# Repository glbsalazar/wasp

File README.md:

# WASP 
## Wireless Assisted Serial Port

---
***This is a Work in Progress***

---
### Motivation
The goal of this project is to have a serial to wireless converter that allows the read and write to a serial port over wifi.

This would allow access to remote devices that do not have a wifi connection or to debug devices that have a permanent serial port and can sometimes crash and lose wifi connectivity (ie: embedded linux systems).

As an end goal this should work in a "ssh" kind of way.

---
### Requirements

* Receive serial data over wifi
* Send serial data over wifi
* Possibiliy to configure the WiFi connection
* Powered over USB or 5V header
* Serial data interface directly on the device

---
### Current implementation
Currently it is based on a STM32 and a ESP-01 for wifi.

The current example works over a tcp connection with the WASP operating as a client.

The current example is based on a fork of the drogue-esp8266 crate with modifications to support version 2.1.0.0 of the ESP-AT firmware

---
## License

### Firmware:

Licensed under either of

- Apache License, Version 2.0 ([LICENSE-APACHE](LICENSE-APACHE) or
  http://www.apache.org/licenses/LICENSE-2.0)

- MIT license ([LICENSE-MIT](LICENSE-MIT) or http://opensource.org/licenses/MIT)

at your option.

### Hardware:

Licensed under CERN Open Hardware License Permissive, Version 2.0 ([LICENSE-CERN-OHL-P](LICENSE-CERN-OHL-P) or
https://ohwr.org/cern_ohl_p_v2.txt)

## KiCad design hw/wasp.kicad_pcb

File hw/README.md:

# WASP 
## Wireless Assisted Serial Port Hardware

---
***This is a Work in Progress***

---

The current design is based around a STM32F103 and has an ESP-01 as a wifi coprocessor

---
## License

Licensed under CERN Open Hardware License Permissive, Version 2.0 ([LICENSE-CERN-OHL-P](LICENSE-CERN-OHL-P) or https://ohwr.org/cern_ohl_p_v2.txt)

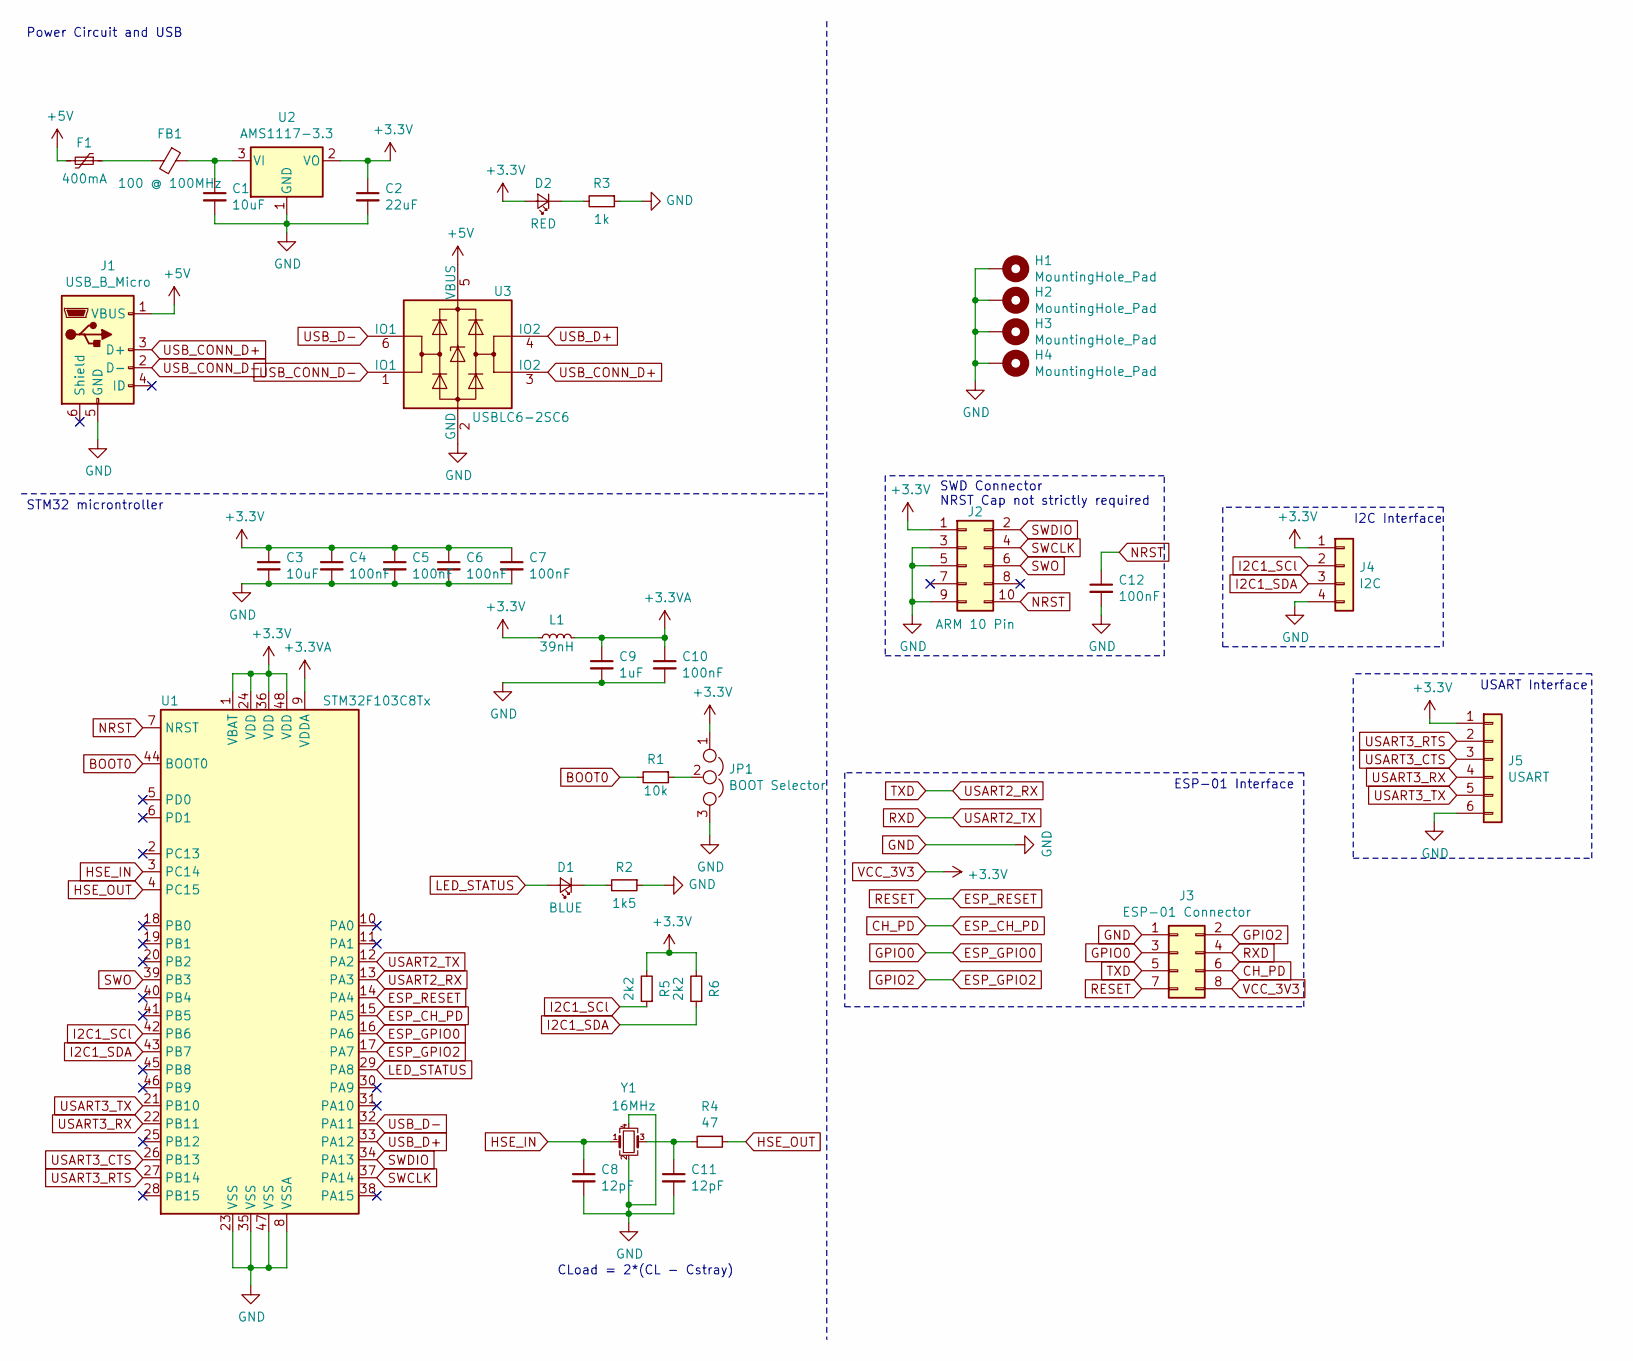
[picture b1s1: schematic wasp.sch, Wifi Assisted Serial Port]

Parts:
C1, C3: 10uF; C_0603_1608Metric; LCSC Part # C19702
C2: 22uF; C_0603_1608Metric; LCSC Part # C59461
C4, C5, C6, C7, C10, C12: 100nF; C_0402_1005Metric; LCSC Part # C1525
C8, C11: 12pF; C_0402_1005Metric; LCSC Part # C1547
C9: 1uF; C_0402_1005Metric; LCSC Part # C52923
D1: BLUE; LED_0603_1608Metric; LCSC Part # C72041
D2: RED; LED_0603_1608Metric; LCSC Part # C2286
F1: 400mA; Fuse_0603_1608Metric
FB1: 100 @ 100MHz; L_0805_2012Metric
H1, H2, H3, H4: MountingHole_Pad; MountingHole_2.2mm_M2_Pad_Via
J1: USB_B_Micro
J2: ARM 10 Pin; PinHeader_2x05_P1.27mm_Vertical_SMD
J3: ESP-01 Connector; PinHeader_2x04_P2.54mm_Vertical
J4: I2C; PinHeader_1x04_P2.54mm_Vertical
J5: USART; PinHeader_1x06_P2.54mm_Horizontal
JP1: BOOT Selector; PinHeader_1x03_P2.54mm_Vertical
L1: 39nH; L_0402_1005Metric
R1: 10k; R_0402_1005Metric
R2: 1k5; R_0603_1608Metric
R3: 1k; R_0603_1608Metric
R4: 47; R_0402_1005Metric
R5, R6: 2k2; R_0402_1005Metric
U1: STM32F103C8Tx; LQFP-48_7x7mm_P0.5mm
U2: AMS1117-3.3; SOT-223-3_TabPin2
U3: USBLC6-2SC6; SOT-23-6
Y1: 16MHz; Crystal_SMD_3225-4Pin_3.2x2.5mm; LCSC Part # C13738

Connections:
+3.3VA: C9.1, C10.1, L1.2, U1.9 (VDDA)
+5V: F1.2, J1.1 (VBUS), U3.5 (VBUS)
BOOT0: R1.2, U1.44 (BOOT0)
CH_PD: J3.6, U1.15 (PA5)
ESP_GPIO0: J3.3, U1.16 (PA6)
ESP_GPIO2: J3.2, U1.17 (PA7)
ESP_RESET: J3.7, U1.14 (PA4)
GND: C1.2, C2.2, C3.2, C4.2, C5.2, C6.2, C7.2, C8.2, C9.2, C10.2, C11.2, C12.2, H1.1, H2.1, H3.1, H4.1, J1.5 (GND), J2.3, J2.5, J2.9, J3.1, J4.4, J5.6, JP1.3, R2.1, R3.1, U1.8 (VSSA), U1.23 (VSS), U1.35 (VSS), U1.47 (VSS), U2.1 (GND), U3.2 (GND), Y1.2, Y1.4
HSE_IN: C8.1, U1.3 (PC14), Y1.1
HSE_OUT: R4.1, U1.4 (PC15)
I2C1_SCl: J4.2, R5.1, U1.42 (PB6)
I2C1_SDA: J4.3, R6.1, U1.43 (PB7)
LED_STATUS: D1.2 (A), U1.29 (PA8)
NRST: C12.1, J2.10, U1.7 (NRST)
unnamed: C1.1, FB1.1, U2.3 (VI)
unnamed: C11.1, R4.2, Y1.3
unnamed: D1.1 (K), R2.2
unnamed: D2.1 (K), R3.2
unnamed: F1.1, FB1.2
unnamed: JP1.2, R1.1
RXD: J3.4, U1.12 (PA2)
SWCLK: J2.4, U1.37 (PA14)
SWDIO: J2.2, U1.34 (PA13)
SWO: J2.6, U1.39 (PB3)
TXD: J3.5, U1.13 (PA3)
USART3_CTS: J5.3, U1.26 (PB13)
USART3_RTS: J5.2, U1.27 (PB14)
USART3_RX: J5.4, U1.22 (PB11)
USART3_TX: J5.5, U1.21 (PB10)
USB_CONN_D+: J1.3 (D+), U3.3 (IO2)
USB_CONN_D-: J1.2 (D-), U3.1 (IO1)
USB_D+: U1.33 (PA12), U3.4 (IO2)
USB_D-: U1.32 (PA11), U3.6 (IO1)
VCC_3V3: C2.1, C3.1, C4.1, C5.1, C6.1, C7.1, D2.2 (A), J2.1, J3.8, J4.1, J5.1, JP1.1, L1.1, R5.2, R6.2, U1.1 (VBAT), U1.24 (VDD), U1.36 (VDD), U1.48 (VDD), U2.2 (VO)

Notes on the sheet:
CLoad = 2*(CL - Cstray)
STM32 microntroller
Power Circuit and USB
SWD Connector NRST Cap not strictly required
ESP-01 Interface
I2C Interface
USART Interface

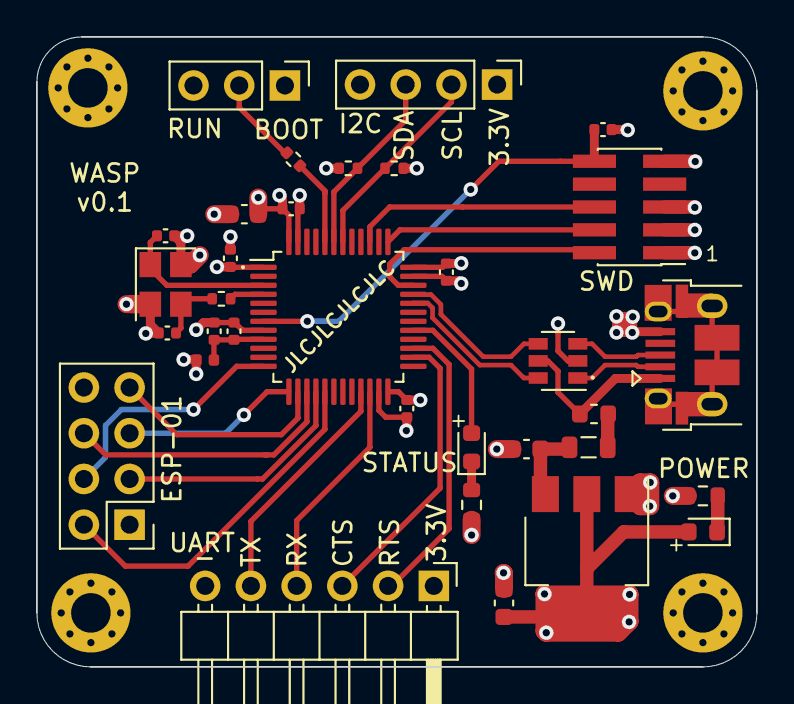
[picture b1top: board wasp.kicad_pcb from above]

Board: 4 copper layers, 40.0 x 35.0 mm, 37 parts (0 on the bottom side), 34 nets.

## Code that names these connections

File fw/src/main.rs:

#![no_main]
#![no_std]


use log::{LevelFilter};
use rtt_logger::RTTLogger;
use rtt_target::rtt_init_print;
use panic_rtt_target as _;

use stm32f4xx_hal::{
    gpio::{gpioa::PA6, Output, PushPull},
    prelude::*,
    serial::{config::Config, Event, Rx, Serial, Tx},
    stm32::*,
};

use rtic::cyccnt::U32Ext;

use drogue_esp8266 as esp8266;
use esp8266::protocol::{Response, WiFiMode};
// TODO: Replace drogue_network with embedded_nal
// use embedded_nal::{TcpServer};
use drogue_network::{
    tcp::{Mode, TcpStack},
    addr::{HostSocketAddr, HostAddr},
};
use core::str::FromStr;
use heapless::consts::{U16, U2,U512};
use heapless::i;
use heapless::spsc::{Producer, Consumer, Queue};

static LOGGER: RTTLogger = RTTLogger::new(LevelFilter::Debug);

const PERIOD: u32 = 50_000_000;
const DIGEST_DELAY: u32 = 200;
const WIFI_SSID: &str = include_str!("wifi.ssid");
const WIFI_PASSWORD: &str = include_str!("wifi.password");
const HOST: &str = "192.168.1.66";

// We need to pass monotonic = rtic::cyccnt::CYCCNT to use schedule feature fo RTIC
#[rtic::app(device = stm32f4xx_hal::stm32, peripherals = true, monotonic = rtic::cyccnt::CYCCNT)]
const APP: () = {
    // Global resources (global variables) are defined here and initialized with the
    // `LateResources` struct in init
    struct Resources {
        led: PA6<Output<PushPull>>,
        adapter: Option<esp8266::adapter::Adapter<'static, Tx<USART2>>>,
        ingress: esp8266::ingress::Ingress<'static, Rx<USART2>>,
        rx_ext: Rx<USART1>,
        usart_ext_producer: Producer<'static, u8, U512>,
        usart_ext_consumer: Consumer<'static, u8, U512>
    }

    #[init(schedule = [blinker], spawn = [digest])]
    fn init(cx: init::Context) -> init::LateResources {
        // hprintln!("init").unwrap();
        rtt_init_print!(BlockIfFull, 4098);
        log::set_logger(&LOGGER).unwrap();
        log::set_max_level(log::LevelFilter::Info);
        log::info!("init");
        // Enable cycle counter
        let mut core = cx.core;
        core.DWT.enable_cycle_counter();

        let device: stm32f4xx_hal::stm32::Peripherals = cx.device;

        // Set up the system clock. We want to run at 48MHz for this one.
        let rcc = device.RCC.constrain();
        let clocks = rcc.cfgr.sysclk(48.mhz()).freeze();

        // Set up the LEDs PA6
        let gpioa = device.GPIOA.split();
        let (tx_esp, rx_esp, tx_ext, rx_ext, mut reset, mut en, mut led) = (
            gpioa.pa2.into_alternate_af7(),
            gpioa.pa3.into_alternate_af7(),
            gpioa.pa9.into_alternate_af7(),
            gpioa.pa10.into_alternate_af7(),
            gpioa.pa4.into_push_pull_output(),
            gpioa.pa5.into_push_pull_output(),
            gpioa.pa6.into_push_pull_output(),
        );

        let mut serial_ext = Serial::usart1(
            device.USART1,
            (tx_ext, rx_ext),
            Config::default().baudrate(115200.bps()),
            clocks,
        )
        .unwrap();

        serial_ext.listen(Event::Rxne);
        let (_tx_ext, rx_ext) = serial_ext.split();

        let mut serial_esp = Serial::usart2(
            device.USART2,
            (tx_esp, rx_esp),
            Config::default().baudrate(921600.bps()),
            clocks,
        )
        .unwrap();

        serial_esp.listen(Event::Rxne);
        let (tx, rx) = serial_esp.split();

        led.set_low().unwrap();

        static mut RESPONSE_QUEUE: Queue<Response, U2> = Queue(i::Queue::new());
        static mut NOTIFICATION_QUEUE: Queue<Response, U16> = Queue(i::Queue::new());
        static mut USART_EXT_QUEUE: Queue<u8, U512> = Queue(i::Queue::new());
        let (usart_ext_producer, usart_ext_consumer) = unsafe { &mut USART_EXT_QUEUE}.split();

        let (adapter, ingress) = esp8266::initialize(
            tx,
            rx,
            &mut en,
            &mut reset,
            unsafe { &mut RESPONSE_QUEUE },
            unsafe { &mut NOTIFICATION_QUEUE },
        )
        .unwrap();

        // Schedule the blinking task
        cx.schedule.blinker(cx.start + PERIOD.cycles()).unwrap();
        cx.spawn.digest().unwrap();

        init::LateResources {
            led: led,
            adapter: Some(adapter),
            ingress: ingress,
            rx_ext: rx_ext,
            usart_ext_producer: usart_ext_producer,
            usart_ext_consumer: usart_ext_consumer,
        }
    }

    #[idle(resources = [adapter, usart_ext_consumer])]
    fn idle(cx: idle::Context) -> ! {
        log::info!("idle");
        let mut adapter = cx.resources.adapter.take().unwrap();

        let result = adapter.get_firmware_info();
        log::info!("firmware: {:?}", result);

        let result = adapter.set_mode(WiFiMode::Station);
        log::info!("set mode {:?}", result);

        let result = adapter.join(WIFI_SSID, WIFI_PASSWORD);
        log::info!("joined wifi {:?}", result);

        let result = adapter.get_ip_address();
        log::info!("IP {:?}", result);

        let network = adapter.into_network_stack();
        log::info!("network initialized");

        let socket = network.open(Mode::Blocking).unwrap();
        log::info!("socket {:?}", socket);

        let socket_addr = HostSocketAddr::new(
            HostAddr::from_str(HOST).unwrap(),
            9999,
        );

        let mut socket = network.connect(socket, socket_addr).unwrap();

        log::info!("socket connected {:?}", socket);

        // Test loop for server
        // for n in 1..2 as u8 {
        //     let mut data: [u8; 12] = Default::default(); 
        //     data.copy_from_slice(b"Hello world0");
        //     data[11] = n;
        //     // let data = r#"{"temp": 41.23}"#;

        //     network.write(&mut socket, &data );
        //     log::info!("wrote");
        //     let mut buffer: [u8; 512] = [0; 512];

        //     log::info!("reading");
        //     match network.read(&mut socket, & mut buffer) {
        //         Ok(len) => log::info!("Received: {}", len),
        //         Err(nb::Error::WouldBlock) => log::error!("WouldBlock"),
        //         Err(_) => log::error!("other")
        //     }

        //     for b in buffer.iter() {
        //         rprint!("{}", *b as char);
        //     }
        //     log::info!("");
        // }

        let mut data = [0; 512];
        
        loop {
            let mut pos = 0;
            while let Some(c) = cx.resources.usart_ext_consumer.dequeue() {
                // log::info!("Received via queue: {}", c as char);
                data[pos] = c;
                pos += 1;
            }
            if pos > 0 {
                network.write(&mut socket, &data[0..pos]).unwrap();
            }
        }

        // network.close(socket);
    }

    #[task(resources = [led], schedule = [blinker])]
    fn blinker(cx: blinker::Context) {
        // Use the safe local `static mut` of RTIC
        static mut LED_STATE: bool = false;

        if *LED_STATE {
            cx.resources.led.set_high().unwrap();
            *LED_STATE = false;
        } else {
            cx.resources.led.set_low().unwrap();
            *LED_STATE = true;
        }
        cx.schedule.blinker(cx.scheduled + PERIOD.cycles()).unwrap();
    }

    #[task(binds = USART1, priority = 10, resources = [rx_ext, usart_ext_producer])]
    fn usart1(ctx: usart1::Context) {
        if let Ok(c) = ctx.resources.rx_ext.read() {
            log::debug!("Received: {}", c as char);
            if let Err(c) = ctx.resources.usart_ext_producer.enqueue(c) {
                log::error!("failed to enqueue character {:?}", c as char);
            }
        } else {
            log::error!("failed to read");
        }
        
        
    }

    #[task(binds = USART2, priority = 10, resources = [ingress])]
    fn usart2(ctx: usart2::Context) {
        if let Err(b) = ctx.resources.ingress.isr() {
            log::error!("failed to ingress {}", b as char);
        }
    }

    #[task(schedule = [digest], priority = 2, resources = [ingress])]
    fn digest(mut ctx: digest::Context) {
        ctx.resources.ingress.lock(|ingress| ingress.digest());
        ctx.schedule
            .digest(ctx.scheduled + (DIGEST_DELAY * 100_000).cycles())
            .unwrap();
    }

    extern "C" {
        fn EXTI0();
        fn EXTI1();
    }
};

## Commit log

2021-02-09 Small README fixes
